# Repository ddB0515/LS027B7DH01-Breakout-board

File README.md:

# LS027B7DH01-Breakout-board
LS027B7DH01 Breakout board

Inspiration from Adafruit breakout board without TTL and usage only of 3.3V (as is needed for my circuit) but can be adopted to use 5V

Using LTC1517-5 (as is suitable for battery power and low consumption)
Note: Instead 3.3uF you can use 4.7uF (tested)

# Interactive BOM
[Interactive BOM](http://htmlpreview.github.io/?https://raw.githubusercontent.com/ddB0515/LS027B7DH01-Breakout-board/main/hardware/bom/ibom.html)

](https://vimeo.com/493829613)

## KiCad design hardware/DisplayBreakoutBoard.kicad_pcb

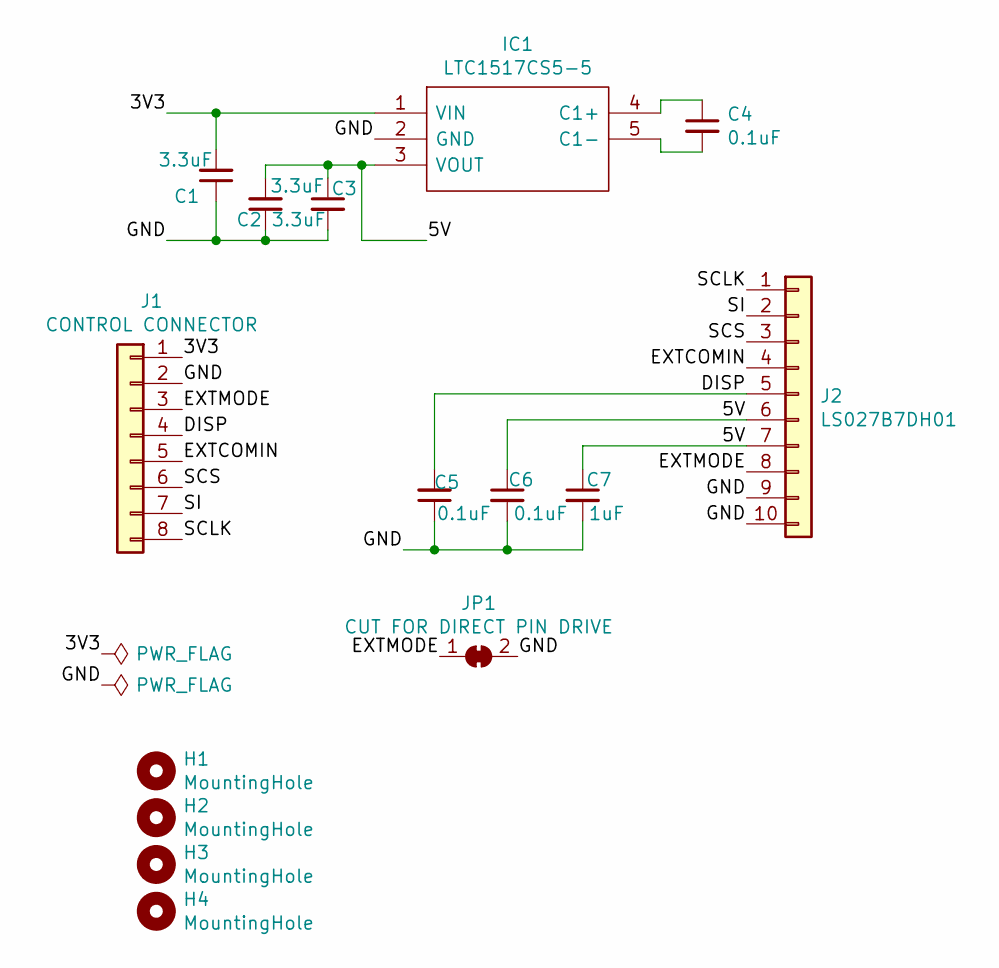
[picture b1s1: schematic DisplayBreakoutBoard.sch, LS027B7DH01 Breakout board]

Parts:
C1, C2, C3: 3.3uF; C_0603_1608Metric
C4, C5, C6: 0.1uF; C_0603_1608Metric
C7: 1uF; C_0603_1608Metric
H1, H2, H3, H4: MountingHole; MountingHole_2.2mm_M2_Pad_Via
IC1: LTC1517CS5-5; SOT-23-5
J1: CONTROL CONNECTOR; PinHeader_1x08_P2.54mm_Vertical
J2: LS027B7DH01; FH12-10S-0.5SH_55
JP1: CUT FOR DIRECT PIN DRIVE; SolderJumper-2_P1.3mm_Bridged_RoundedPad1.0x1.5mm

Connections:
/3V3: C1.2, IC1.1 (VIN), J1.1
/5V: C2.2, C3.1, C6.1, C7.1, IC1.3 (VOUT), J2.6, J2.7
/DISP: C5.2, J1.4, J2.5
/EXTCOMIN: J1.5, J2.4
/EXTMODE: J1.3, J2.8, JP1.1 (A)
/GND: C1.1, C2.1, C3.2, C5.1, C6.2, C7.2, IC1.2 (GND), J1.2, J2.9, J2.10, JP1.2 (B)
/SCLK: J1.8, J2.1
/SCS: J1.6, J2.3
/SI: J1.7, J2.2
unnamed: C4.1, IC1.4 (C1+)
unnamed: C4.2, IC1.5 (C1-)

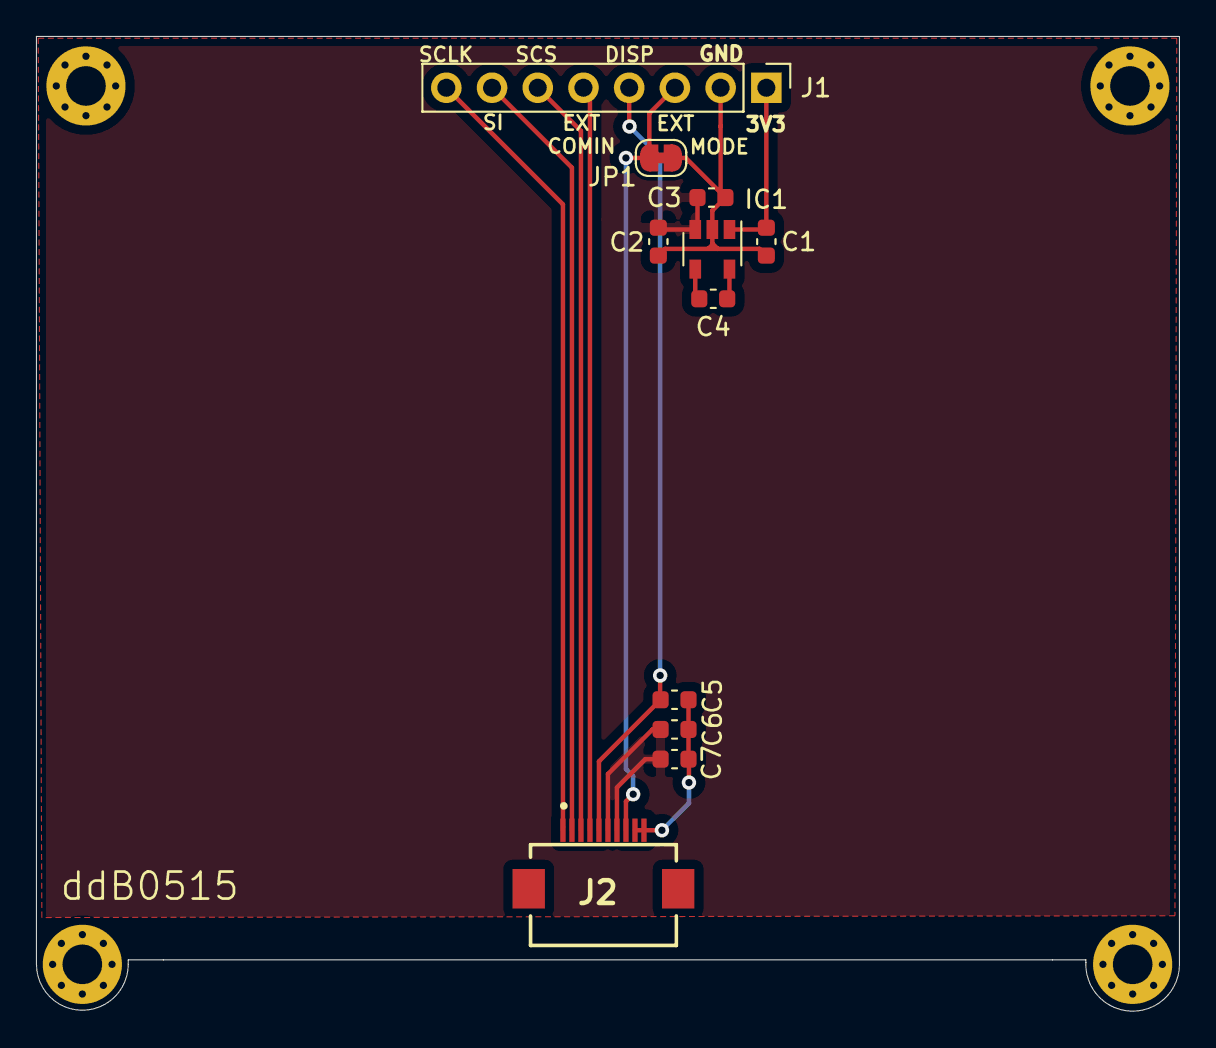
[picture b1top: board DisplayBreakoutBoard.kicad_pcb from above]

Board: 2 copper layers, 63.5 x 54.2 mm, 15 parts (0 on the bottom side), 11 nets.

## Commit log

2020-12-22 added animation
2020-12-22 forgot extension
